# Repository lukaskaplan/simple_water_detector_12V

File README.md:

# simple_water_detector_12V

## Description

Simple water detector with 12V logic.

It is designed to be used with I/O modules [Papouch Quido ETH](https://papouch.com/io-moduly/quido/ethernet/) (12V inputs). 

## Usage example

Monitoring the server room environment for the presence of water on the floor. Water may occur in the server room, for example, due to condensation leakage from the air conditioning. Therefore, we can monitor areas at risk of water occurrence using this water detector.

Detection "probes" are attached to the floor and connected to the detector. Self-adhesive aluminum tape can be used as probes. (It can be purchased at an air ventilation store).

**Note that if an antistatic floor is used in the server room, it is necessary to isolate the aluminum tape from the floor.** It is best to do this by applying some non-conductive tape underneath. I do not recommend "Duck tape" because it is hydrophobic and prevents water from forming a puddle that would connect the electrodes. Ordinary transparent tape, commonly used for packages, has proven to be the most effective.

The output from the detector is connected to an I/O module. This module is then capable of sending an SNMP trap to Zabbix upon flood detection, thus alerting the monitoring team to the water leak problem.

## Installation

## Schematics

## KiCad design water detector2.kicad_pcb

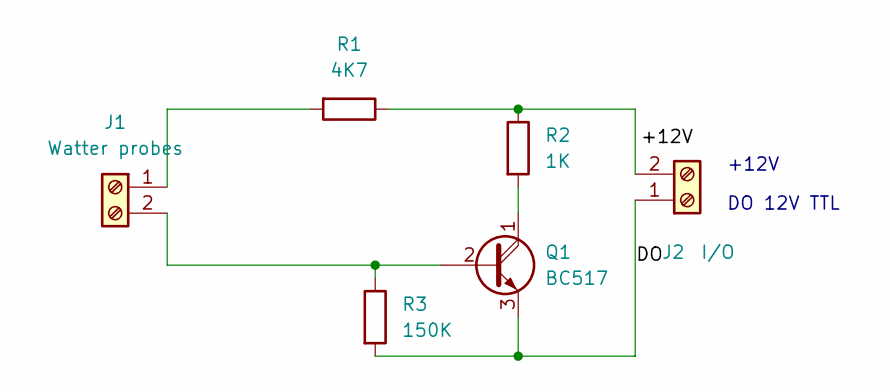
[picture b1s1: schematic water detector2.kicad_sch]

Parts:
J1: Watter probes; TerminalBlock_Phoenix_MKDS-1,5-2-5.08_1x02_P5.08mm_Horizont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
J2: I/O; TerminalBlock_Phoenix_MKDS-1,5-2-5.08_1x02_P5.08mm_Horizont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
Q1: BC517; TO-92_Inline
R1: 4K7; R_Axial_DIN0207_L6.3mm_D2.5mm_P7.62mm_Horizontal
R2: 1K; R_Axial_DIN0207_L6.3mm_D2.5mm_P7.62mm_Horizontal
R3: 150K; R_Axial_DIN0207_L6.3mm_D2.5mm_P7.62mm_Horizontal

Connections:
/DO: J2.1, Q1.3 (E), R3.2
unnamed: Q1.1 (C), R2.2
unnamed: J1.2, Q1.2 (B), R3.1
unnamed: J2.2, R1.1, R2.1
unnamed: J1.1, R1.2

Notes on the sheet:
+12V
DO 12V TTL

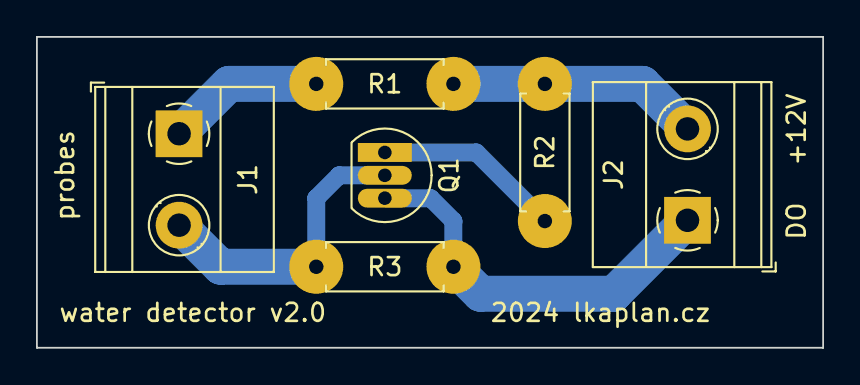
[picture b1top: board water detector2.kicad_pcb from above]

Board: 2 copper layers, 43.7 x 17.3 mm, 6 parts (0 on the bottom side), 5 nets.

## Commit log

2024-04-26 Update Readme + photos
